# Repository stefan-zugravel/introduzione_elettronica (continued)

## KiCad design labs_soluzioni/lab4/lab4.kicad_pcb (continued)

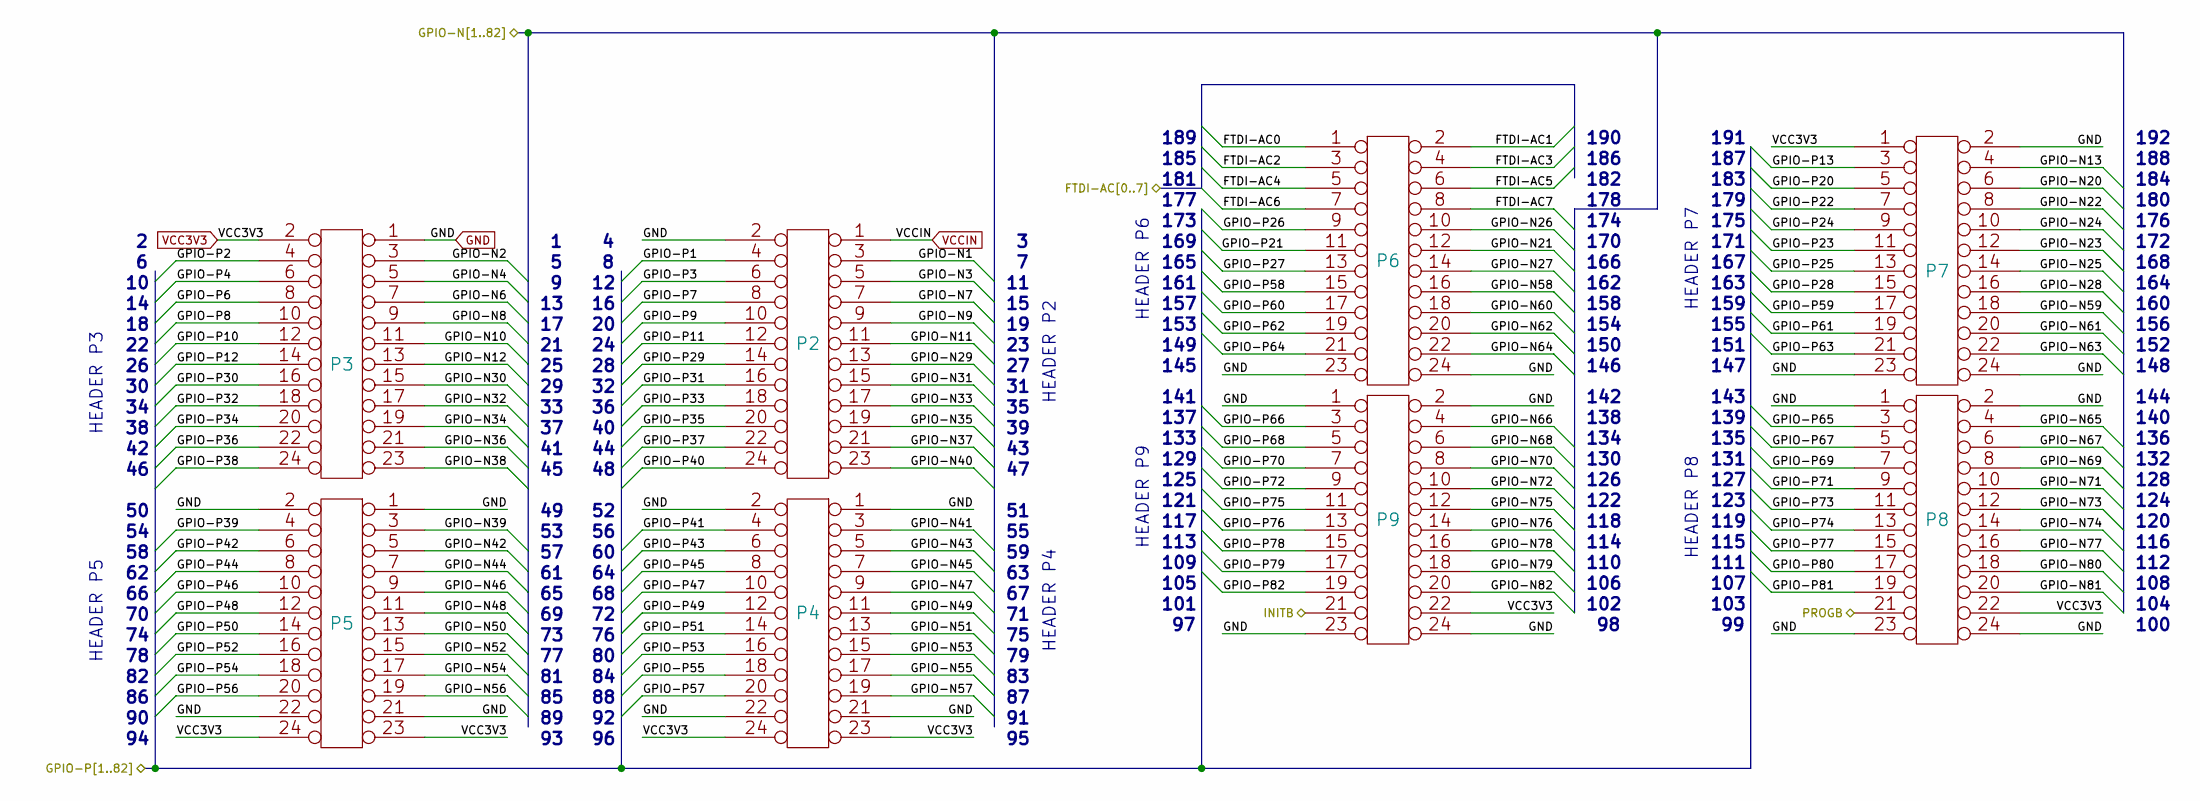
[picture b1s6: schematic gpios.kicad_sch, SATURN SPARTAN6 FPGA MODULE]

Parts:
P2, P3, P4, P5, P6, P7, P8, P9: CONN_12X2

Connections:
/FTDI2232H/FTDI-AC0: P6.1; also elsewhere on the board
/FTDI2232H/FTDI-AC1: P6.2; also elsewhere on the board
/FTDI2232H/FTDI-AC2: P6.3; also elsewhere on the board
/FTDI2232H/FTDI-AC3: P6.4; also elsewhere on the board
/FTDI2232H/FTDI-AC4: P6.5; also elsewhere on the board
/FTDI2232H/FTDI-AC5: P6.6; also elsewhere on the board
/FTDI2232H/FTDI-AC6: P6.7; also elsewhere on the board
/FTDI2232H/FTDI-AC7: P6.8; also elsewhere on the board
/FTDI2232H/PROGB: P8.21; also elsewhere on the board
/GPIOS/GPIO-N1: P2.3; also elsewhere on the board
/GPIOS/GPIO-N2: P3.3; also elsewhere on the board
/GPIOS/GPIO-N3: P2.5; also elsewhere on the board
/GPIOS/GPIO-N4: P3.5; also elsewhere on the board
/GPIOS/GPIO-N6: P3.7; also elsewhere on the board
/GPIOS/GPIO-N7: P2.7; also elsewhere on the board
/GPIOS/GPIO-N8: P3.9; also elsewhere on the board
/GPIOS/GPIO-N9: P2.9; also elsewhere on the board
/GPIOS/GPIO-N10: P3.11; also elsewhere on the board
/GPIOS/GPIO-N11: P2.11; also elsewhere on the board
/GPIOS/GPIO-N12: P3.13; also elsewhere on the board
/GPIOS/GPIO-N13: P7.4; also elsewhere on the board
/GPIOS/GPIO-N20: P7.6; also elsewhere on the board
/GPIOS/GPIO-N21: P6.12; also elsewhere on the board
/GPIOS/GPIO-N22: P7.8; also elsewhere on the board
/GPIOS/GPIO-N23: P7.12; also elsewhere on the board
/GPIOS/GPIO-N24: P7.10; also elsewhere on the board
/GPIOS/GPIO-N25: P7.14; also elsewhere on the board
/GPIOS/GPIO-N26: P6.10; also elsewhere on the board
/GPIOS/GPIO-N27: P6.14; also elsewhere on the board
/GPIOS/GPIO-N28: P7.16; also elsewhere on the board
/GPIOS/GPIO-N29: P2.13; also elsewhere on the board
/GPIOS/GPIO-N30: P3.15; also elsewhere on the board
/GPIOS/GPIO-N31: P2.15; also elsewhere on the board
/GPIOS/GPIO-N32: P3.17; also elsewhere on the board
/GPIOS/GPIO-N33: P2.17; also elsewhere on the board
/GPIOS/GPIO-N34: P3.19; also elsewhere on the board
/GPIOS/GPIO-N35: P2.19; also elsewhere on the board
/GPIOS/GPIO-N36: P3.21; also elsewhere on the board
/GPIOS/GPIO-N37: P2.21; also elsewhere on the board
/GPIOS/GPIO-N38: P3.23; also elsewhere on the board
/GPIOS/GPIO-N39: P5.3; also elsewhere on the board
/GPIOS/GPIO-N40: P2.23; also elsewhere on the board
/GPIOS/GPIO-N41: P4.3; also elsewhere on the board
/GPIOS/GPIO-N42: P5.5; also elsewhere on the board
/GPIOS/GPIO-N43: P4.5; also elsewhere on the board
/GPIOS/GPIO-N44: P5.7; also elsewhere on the board
/GPIOS/GPIO-N45: P4.7; also elsewhere on the board
/GPIOS/GPIO-N46: P5.9; also elsewhere on the board
/GPIOS/GPIO-N47: P4.9; also elsewhere on the board
/GPIOS/GPIO-N48: P5.11; also elsewhere on the board
/GPIOS/GPIO-N49: P4.11; also elsewhere on the board
/GPIOS/GPIO-N50: P5.13; also elsewhere on the board
/GPIOS/GPIO-N51: P4.13; also elsewhere on the board
/GPIOS/GPIO-N52: P5.15; also elsewhere on the board
/GPIOS/GPIO-N53: P4.15; also elsewhere on the board
/GPIOS/GPIO-N54: P5.17; also elsewhere on the board
/GPIOS/GPIO-N55: P4.17; also elsewhere on the board
/GPIOS/GPIO-N56: P5.19; also elsewhere on the board
/GPIOS/GPIO-N57: P4.19; also elsewhere on the board
/GPIOS/GPIO-N58: P6.16; also elsewhere on the board
/GPIOS/GPIO-N59: P7.18; also elsewhere on the board
/GPIOS/GPIO-N60: P6.18; also elsewhere on the board
/GPIOS/GPIO-N61: P7.20; also elsewhere on the board
/GPIOS/GPIO-N62: P6.20; also elsewhere on the board
/GPIOS/GPIO-N63: P7.22; also elsewhere on the board
/GPIOS/GPIO-N64: P6.22; also elsewhere on the board
/GPIOS/GPIO-N65: P8.4; also elsewhere on the board
/GPIOS/GPIO-N66: P9.4; also elsewhere on the board
/GPIOS/GPIO-N67: P8.6; also elsewhere on the board
/GPIOS/GPIO-N68: P9.6; also elsewhere on the board
/GPIOS/GPIO-N69: P8.8; also elsewhere on the board
/GPIOS/GPIO-N70: P9.8; also elsewhere on the board
/GPIOS/GPIO-N71: P8.10; also elsewhere on the board
/GPIOS/GPIO-N72: P9.10; also elsewhere on the board
/GPIOS/GPIO-N73: P8.12; also elsewhere on the board
/GPIOS/GPIO-N74: P8.14; also elsewhere on the board
/GPIOS/GPIO-N75: P9.12; also elsewhere on the board
/GPIOS/GPIO-N76: P9.14; also elsewhere on the board
/GPIOS/GPIO-N77: P8.16; also elsewhere on the board
/GPIOS/GPIO-N78: P9.16; also elsewhere on the board
/GPIOS/GPIO-N79: P9.18; also elsewhere on the board
/GPIOS/GPIO-N80: P8.18; also elsewhere on the board
/GPIOS/GPIO-N81: P8.20; also elsewhere on the board
/GPIOS/GPIO-N82: P9.20; also elsewhere on the board
/GPIOS/GPIO-P1: P2.4; also elsewhere on the board
/GPIOS/GPIO-P2: P3.4; also elsewhere on the board
/GPIOS/GPIO-P3: P2.6; also elsewhere on the board
/GPIOS/GPIO-P4: P3.6; also elsewhere on the board
/GPIOS/GPIO-P6: P3.8; also elsewhere on the board
/GPIOS/GPIO-P7: P2.8; also elsewhere on the board
/GPIOS/GPIO-P8: P3.10; also elsewhere on the board
/GPIOS/GPIO-P9: P2.10; also elsewhere on the board
/GPIOS/GPIO-P10: P3.12; also elsewhere on the board
/GPIOS/GPIO-P11: P2.12; also elsewhere on the board
/GPIOS/GPIO-P12: P3.14; also elsewhere on the board
/GPIOS/GPIO-P13: P7.3; also elsewhere on the board
/GPIOS/GPIO-P20: P7.5; also elsewhere on the board
/GPIOS/GPIO-P21: P6.11; also elsewhere on the board
/GPIOS/GPIO-P22: P7.7; also elsewhere on the board
/GPIOS/GPIO-P23: P7.11; also elsewhere on the board
/GPIOS/GPIO-P24: P7.9; also elsewhere on the board
/GPIOS/GPIO-P25: P7.13; also elsewhere on the board
/GPIOS/GPIO-P26: P6.9; also elsewhere on the board
/GPIOS/GPIO-P27: P6.13; also elsewhere on the board
/GPIOS/GPIO-P28: P7.15; also elsewhere on the board
/GPIOS/GPIO-P29: P2.14; also elsewhere on the board
/GPIOS/GPIO-P30: P3.16; also elsewhere on the board
/GPIOS/GPIO-P31: P2.16; also elsewhere on the board
/GPIOS/GPIO-P32: P3.18; also elsewhere on the board
/GPIOS/GPIO-P33: P2.18; also elsewhere on the board
/GPIOS/GPIO-P34: P3.20; also elsewhere on the board
/GPIOS/GPIO-P35: P2.20; also elsewhere on the board
/GPIOS/GPIO-P36: P3.22; also elsewhere on the board
/GPIOS/GPIO-P37: P2.22; also elsewhere on the board
/GPIOS/GPIO-P38: P3.24; also elsewhere on the board
/GPIOS/GPIO-P39: P5.4; also elsewhere on the board
/GPIOS/GPIO-P40: P2.24; also elsewhere on the board
/GPIOS/GPIO-P41: P4.4; also elsewhere on the board
/GPIOS/GPIO-P42: P5.6; also elsewhere on the board
/GPIOS/GPIO-P43: P4.6; also elsewhere on the board
/GPIOS/GPIO-P44: P5.8; also elsewhere on the board
/GPIOS/GPIO-P45: P4.8; also elsewhere on the board
/GPIOS/GPIO-P46: P5.10; also elsewhere on the board
/GPIOS/GPIO-P47: P4.10; also elsewhere on the board
/GPIOS/GPIO-P48: P5.12; also elsewhere on the board
/GPIOS/GPIO-P49: P4.12; also elsewhere on the board
/GPIOS/GPIO-P50: P5.14; also elsewhere on the board
/GPIOS/GPIO-P51: P4.14; also elsewhere on the board
/GPIOS/GPIO-P52: P5.16; also elsewhere on the board
/GPIOS/GPIO-P53: P4.16; also elsewhere on the board
/GPIOS/GPIO-P54: P5.18; also elsewhere on the board
/GPIOS/GPIO-P55: P4.18; also elsewhere on the board
/GPIOS/GPIO-P56: P5.20; also elsewhere on the board
/GPIOS/GPIO-P57: P4.20; also elsewhere on the board
/GPIOS/GPIO-P58: P6.15; also elsewhere on the board
/GPIOS/GPIO-P59: P7.17; also elsewhere on the board
/GPIOS/GPIO-P60: P6.17; also elsewhere on the board
/GPIOS/GPIO-P61: P7.19; also elsewhere on the board
/GPIOS/GPIO-P62: P6.19; also elsewhere on the board
/GPIOS/GPIO-P63: P7.21; also elsewhere on the board
/GPIOS/GPIO-P64: P6.21; also elsewhere on the board
/GPIOS/GPIO-P65: P8.3; also elsewhere on the board
/GPIOS/GPIO-P66: P9.3; also elsewhere on the board
/GPIOS/GPIO-P67: P8.5; also elsewhere on the board
/GPIOS/GPIO-P68: P9.5; also elsewhere on the board
/GPIOS/GPIO-P69: P8.7; also elsewhere on the board
/GPIOS/GPIO-P70: P9.7; also elsewhere on the board
/GPIOS/GPIO-P71: P8.9; also elsewhere on the board
/GPIOS/GPIO-P72: P9.9; also elsewhere on the board
/GPIOS/GPIO-P73: P8.11; also elsewhere on the board
/GPIOS/GPIO-P74: P8.13; also elsewhere on the board
/GPIOS/GPIO-P75: P9.11; also elsewhere on the board
/GPIOS/GPIO-P76: P9.13; also elsewhere on the board
/GPIOS/GPIO-P77: P8.15; also elsewhere on the board
/GPIOS/GPIO-P78: P9.15; also elsewhere on the board
/GPIOS/GPIO-P79: P9.17; also elsewhere on the board
/GPIOS/GPIO-P80: P8.17; also elsewhere on the board
/GPIOS/GPIO-P81: P8.19; also elsewhere on the board
/GPIOS/GPIO-P82: P9.19; also elsewhere on the board
/GPIOS/INITB: P9.21; also elsewhere on the board
GND: P2.2, P3.1, P4.1, P4.2, P4.21, P4.22, P5.1, P5.2, P5.21, P5.22, P6.23, P6.24, P7.2, P7.23, P7.24, P8.1, P8.2, P8.23, P8.24, P9.1, P9.2, P9.23, P9.24; also elsewhere on the board
VCC3V3: P3.2, P4.23, P4.24, P5.23, P5.24, P7.1, P8.22, P9.22; also elsewhere on the board
VCCIN: P2.1; also elsewhere on the board

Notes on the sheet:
141
129
132
116
112
184
150
187
139
115
100
127
111
179
120
175
183
180
162
154
134
192
157
155
113
101
148
105
HEADER P7
128
176
189
163
107
143
123
174
HEADER P9
190
104

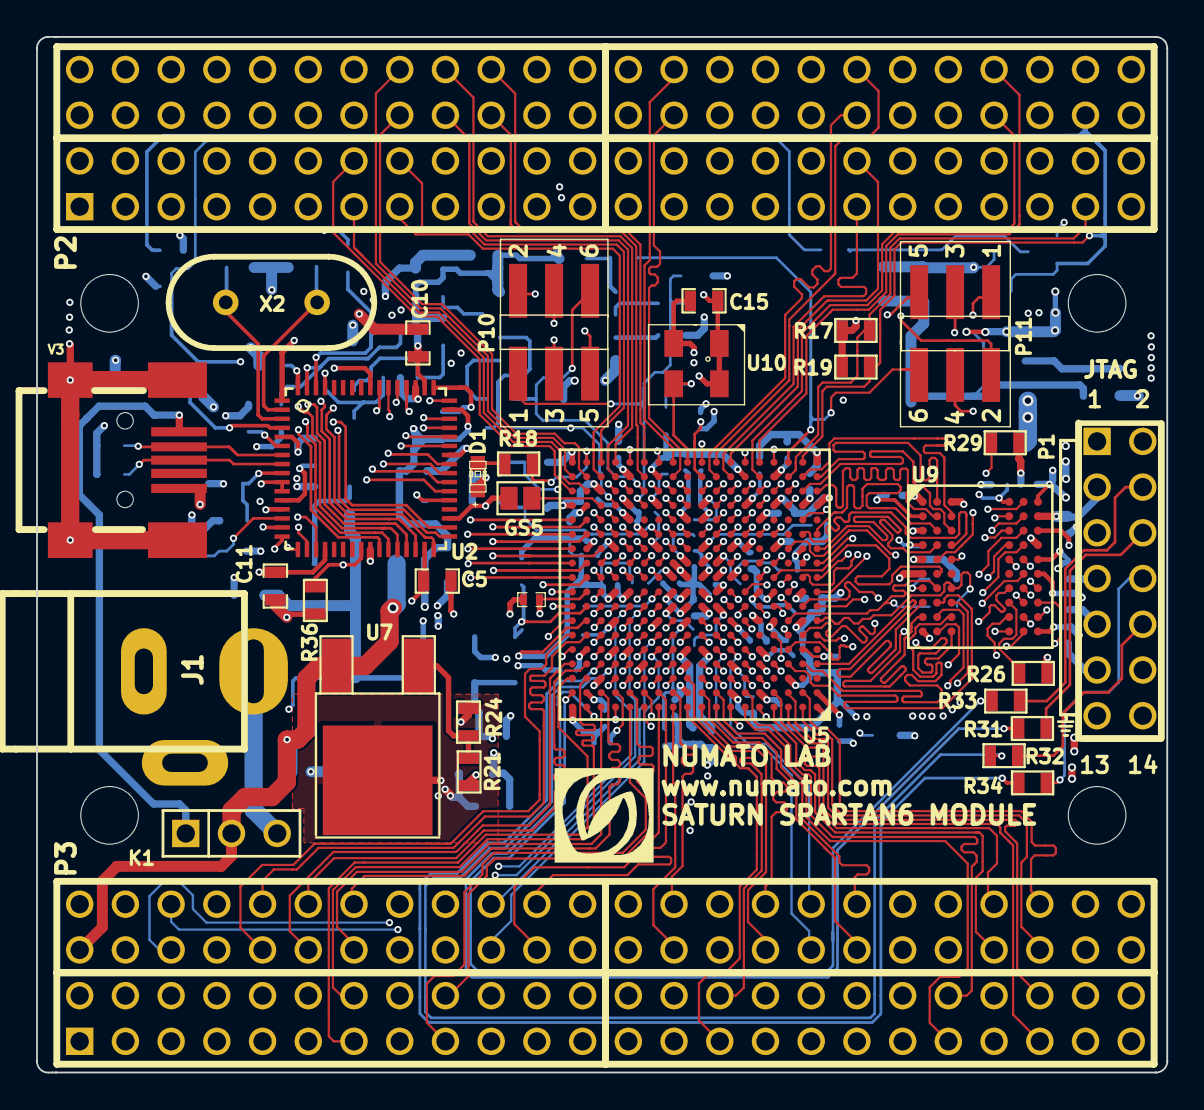
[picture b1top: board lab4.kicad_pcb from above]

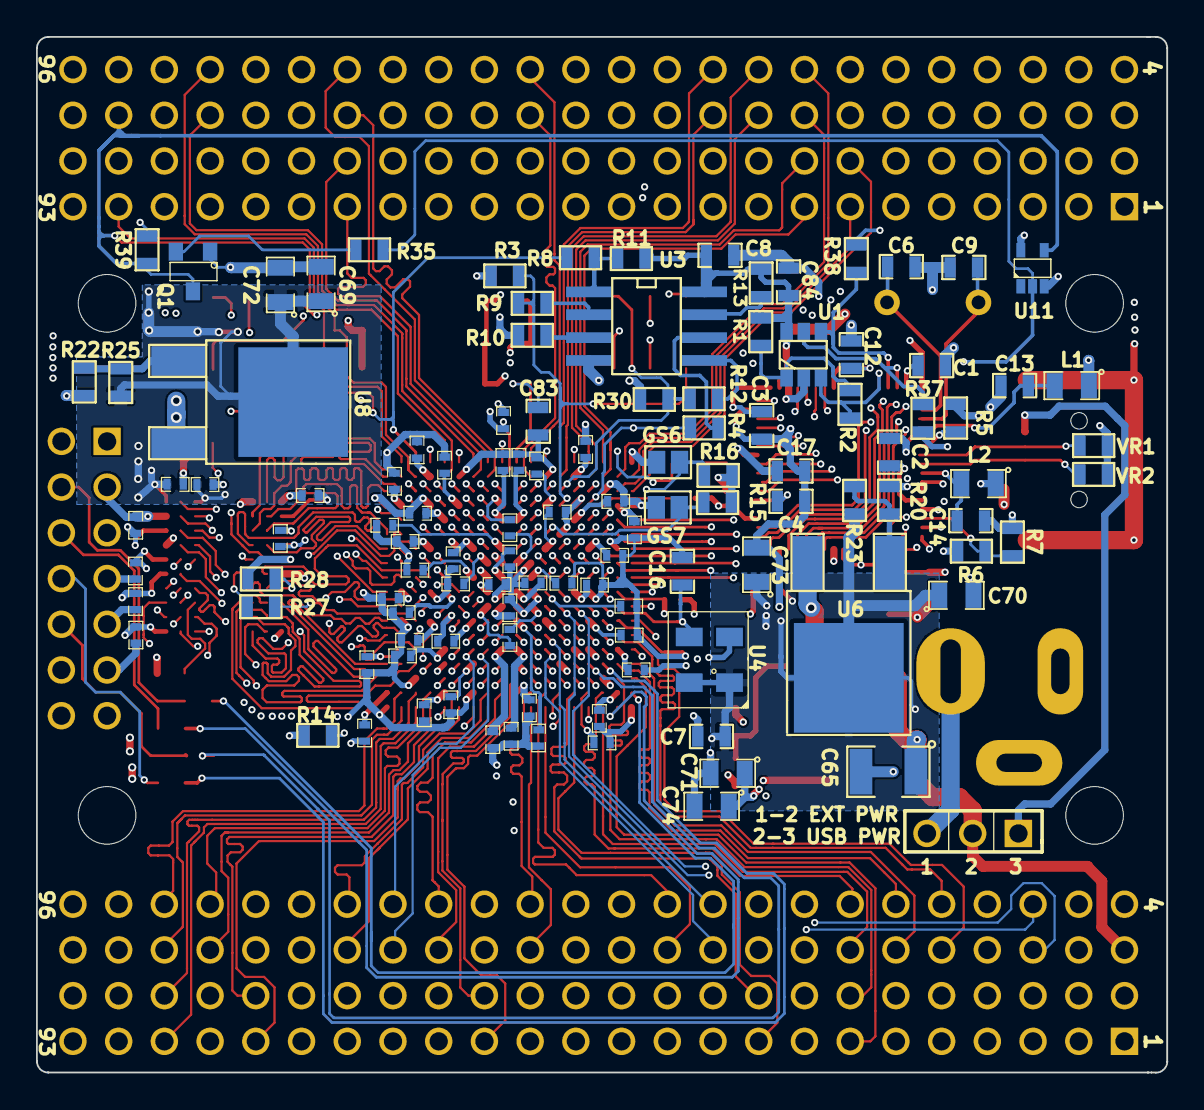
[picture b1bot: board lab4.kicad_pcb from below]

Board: 6 copper layers, 62.8 x 57.5 mm, 157 parts (114 on the bottom side), 271 nets.

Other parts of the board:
1PIN, 1PIN#2, 1PIN#3, 1PIN#4: P***; MH-3.2MM
U5: SPARTAN6LXXXX-CSG324; CSG324

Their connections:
/FTDI2232H/PROGB: U5.V2; also elsewhere on the board
/FTDI2232H/U1-CS: U5.V3; also elsewhere on the board
/FTDI2232H/U1-D0: U5.L17; also elsewhere on the board
/FTDI2232H/U1-D1: U5.L18; also elsewhere on the board
/FTDI2232H/U1-D2: U5.M16; also elsewhere on the board
/FTDI2232H/U1-D3: U5.M18; also elsewhere on the board
/FTDI2232H/U1-D4: U5.N17; also elsewhere on the board
/FTDI2232H/U1-D5: U5.N18; also elsewhere on the board
/FTDI2232H/U1-D6: U5.P17; also elsewhere on the board
/FTDI2232H/U1-D7: U5.P18; also elsewhere on the board
/FTDI2232H/U1-RD#: U5.J18; also elsewhere on the board
/FTDI2232H/U1-RXF#: U5.K18; also elsewhere on the board
/FTDI2232H/U1-SCK: U5.R15; also elsewhere on the board
/FTDI2232H/U1-SDI: U5.R13; also elsewhere on the board
/FTDI2232H/U1-SDO: U5.T13; also elsewhere on the board
/FTDI2232H/U1-SIWUB: U5.H18; also elsewhere on the board
/FTDI2232H/U1-TXE#: U5.K17; also elsewhere on the board
/FTDI2232H/U1-WR#: U5.J16; also elsewhere on the board
/GPIOS/GPIO-N1: U5.K14; also elsewhere on the board
/GPIOS/GPIO-N2: U5.G13; also elsewhere on the board
/GPIOS/GPIO-N3: U5.H14; also elsewhere on the board
/GPIOS/GPIO-N4: U5.H16; also elsewhere on the board
/GPIOS/GPIO-N6: U5.G14; also elsewhere on the board
/GPIOS/GPIO-N7: U5.G18; also elsewhere on the board
/GPIOS/GPIO-N8: U5.F16; also elsewhere on the board
/GPIOS/GPIO-N9: U5.F18; also elsewhere on the board
/GPIOS/GPIO-N10: U5.E18; also elsewhere on the board
/GPIOS/GPIO-N11: U5.D18; also elsewhere on the board
/GPIOS/GPIO-N12: U5.C18; also elsewhere on the board
/GPIOS/GPIO-N13: U5.K13; also elsewhere on the board
/GPIOS/GPIO-N20: U5.M13; also elsewhere on the board
/GPIOS/GPIO-N21: U5.K16; also elsewhere on the board
/GPIOS/GPIO-N22: U5.N14; also elsewhere on the board
/GPIOS/GPIO-N23: U5.N16; also elsewhere on the board
/GPIOS/GPIO-N24: U5.L16; also elsewhere on the board
/GPIOS/GPIO-N25: U5.P16; also elsewhere on the board
/GPIOS/GPIO-N26: U5.L13; also elsewhere on the board
/GPIOS/GPIO-N27: U5.T18; also elsewhere on the board
/GPIOS/GPIO-N28: U5.U18; also elsewhere on the board
/GPIOS/GPIO-N29: U5.A16; also elsewhere on the board
/GPIOS/GPIO-N30: U5.A15; also elsewhere on the board
/GPIOS/GPIO-N31: U5.C14; also elsewhere on the board
/GPIOS/GPIO-N32: U5.A14; also elsewhere on the board
/GPIOS/GPIO-N33: U5.E13; also elsewhere on the board
/GPIOS/GPIO-N34: U5.A13; also elsewhere on the board
/GPIOS/GPIO-N35: U5.E12; also elsewhere on the board
/GPIOS/GPIO-N36: U5.C12; also elsewhere on the board
/GPIOS/GPIO-N37: U5.A12; also elsewhere on the board
/GPIOS/GPIO-N38: U5.E11; also elsewhere on the board
/GPIOS/GPIO-N39: U5.F10; also elsewhere on the board
/GPIOS/GPIO-N40: U5.C11; also elsewhere on the board
/GPIOS/GPIO-N41: U5.A11; also elsewhere on the board
/GPIOS/GPIO-N42: U5.A10; also elsewhere on the board
/GPIOS/GPIO-N43: U5.F9; also elsewhere on the board
/GPIOS/GPIO-N44: U5.C9; also elsewhere on the board
/GPIOS/GPIO-N45: U5.A9; also elsewhere on the board
/GPIOS/GPIO-N46: U5.F8; also elsewhere on the board
/GPIOS/GPIO-N47: U5.E8; also elsewhere on the board
/GPIOS/GPIO-N48: U5.C8; also elsewhere on the board
/GPIOS/GPIO-N49: U5.A8; also elsewhere on the board
/GPIOS/GPIO-N50: U5.E6; also elsewhere on the board
/GPIOS/GPIO-N51: U5.A7; also elsewhere on the board
/GPIOS/GPIO-N52: U5.A6; also elsewhere on the board
/GPIOS/GPIO-N53: U5.C6; also elsewhere on the board
/GPIOS/GPIO-N54: U5.A5; also elsewhere on the board
/GPIOS/GPIO-N55: U5.A4; also elsewhere on the board
/GPIOS/GPIO-N56: U5.A3; also elsewhere on the board
/GPIOS/GPIO-N57: U5.A2; also elsewhere on the board
/GPIOS/GPIO-N58: U5.V16; also elsewhere on the board
/GPIOS/GPIO-N59: U5.V15; also elsewhere on the board
/GPIOS/GPIO-N60: U5.V14; also elsewhere on the board
/GPIOS/GPIO-N61: U5.V13; also elsewhere on the board
/GPIOS/GPIO-N62: U5.V12; also elsewhere on the board
/GPIOS/GPIO-N63: U5.N11; also elsewhere on the board
/GPIOS/GPIO-N64: U5.T11; also elsewhere on the board
/GPIOS/GPIO-N65: U5.V11; also elsewhere on the board
/GPIOS/GPIO-N66: U5.P11; also elsewhere on the board
/GPIOS/GPIO-N67: U5.N9; also elsewhere on the board
/GPIOS/GPIO-N68: U5.T10; also elsewhere on the board
/GPIOS/GPIO-N69: U5.T8; also elsewhere on the board
/GPIOS/GPIO-N70: U5.V9; also elsewhere on the board
/GPIOS/GPIO-N71: U5.N8; also elsewhere on the board
/GPIOS/GPIO-N72: U5.P8; also elsewhere on the board
/GPIOS/GPIO-N73: U5.V8; also elsewhere on the board
/GPIOS/GPIO-N74: U5.P7; also elsewhere on the board
/GPIOS/GPIO-N75: U5.V7; also elsewhere on the board
/GPIOS/GPIO-N76: U5.T7; also elsewhere on the board
/GPIOS/GPIO-N77: U5.V6; also elsewhere on the board
/GPIOS/GPIO-N78: U5.P6; also elsewhere on the board
/GPIOS/GPIO-N79: U5.T5; also elsewhere on the board
/GPIOS/GPIO-N80: U5.V5; also elsewhere on the board
/GPIOS/GPIO-N81: U5.V4; also elsewhere on the board
/GPIOS/GPIO-N82: U5.T3; also elsewhere on the board
/GPIOS/GPIO-P1: U5.J13; also elsewhere on the board
/GPIOS/GPIO-P2: U5.H12; also elsewhere on the board
/GPIOS/GPIO-P3: U5.H13; also elsewhere on the board
/GPIOS/GPIO-P4: U5.H15; also elsewhere on the board
/GPIOS/GPIO-P6: U5.F14; also elsewhere on the board
/GPIOS/GPIO-P7: U5.G16; also elsewhere on the board
/GPIOS/GPIO-P8: U5.F15; also elsewhere on the board
/GPIOS/GPIO-P9: U5.F17; also elsewhere on the board
/GPIOS/GPIO-P10: U5.E16; also elsewhere on the board
/GPIOS/GPIO-P11: U5.D17; also elsewhere on the board
/GPIOS/GPIO-P12: U5.C17; also elsewhere on the board
/GPIOS/GPIO-P13: U5.K12; also elsewhere on the board
/GPIOS/GPIO-P20: U5.L14; also elsewhere on the board
/GPIOS/GPIO-P21: U5.K15; also elsewhere on the board
/GPIOS/GPIO-P22: U5.M14; also elsewhere on the board
/GPIOS/GPIO-P23: U5.N15; also elsewhere on the board
/GPIOS/GPIO-P24: U5.L15; also elsewhere on the board
/GPIOS/GPIO-P25: U5.P15; also elsewhere on the board
/GPIOS/GPIO-P26: U5.L12; also elsewhere on the board
/GPIOS/GPIO-P27: U5.T17; also elsewhere on the board
/GPIOS/GPIO-P28: U5.U17; also elsewhere on the board
/GPIOS/GPIO-P29: U5.B16; also elsewhere on the board
/GPIOS/GPIO-P30: U5.C15; also elsewhere on the board
/GPIOS/GPIO-P31: U5.D14; also elsewhere on the board
/GPIOS/GPIO-P32: U5.B14; also elsewhere on the board
/GPIOS/GPIO-P33: U5.F13; also elsewhere on the board
/GPIOS/GPIO-P34: U5.C13; also elsewhere on the board
/GPIOS/GPIO-P35: U5.F12; also elsewhere on the board
/GPIOS/GPIO-P36: U5.D12; also elsewhere on the board
/GPIOS/GPIO-P37: U5.B12; also elsewhere on the board
/GPIOS/GPIO-P38: U5.F11; also elsewhere on the board
/GPIOS/GPIO-P39: U5.G11; also elsewhere on the board
/GPIOS/GPIO-P40: U5.D11; also elsewhere on the board
/GPIOS/GPIO-P41: U5.B11; also elsewhere on the board
/GPIOS/GPIO-P42: U5.C10; also elsewhere on the board
/GPIOS/GPIO-P43: U5.G9; also elsewhere on the board
/GPIOS/GPIO-P44: U5.D9; also elsewhere on the board
/GPIOS/GPIO-P45: U5.B9; also elsewhere on the board
/GPIOS/GPIO-P46: U5.G8; also elsewhere on the board
/GPIOS/GPIO-P47: U5.E7; also elsewhere on the board
/GPIOS/GPIO-P48: U5.D8; also elsewhere on the board
/GPIOS/GPIO-P49: U5.B8; also elsewhere on the board
/GPIOS/GPIO-P50: U5.F7; also elsewhere on the board
/GPIOS/GPIO-P51: U5.C7; also elsewhere on the board
/GPIOS/GPIO-P52: U5.B6; also elsewhere on the board
/GPIOS/GPIO-P53: U5.D6; also elsewhere on the board
/GPIOS/GPIO-P54: U5.C5; also elsewhere on the board
/GPIOS/GPIO-P55: U5.B4; also elsewhere on the board
/GPIOS/GPIO-P56: U5.B3; also elsewhere on the board
/GPIOS/GPIO-P57: U5.B2; also elsewhere on the board
/GPIOS/GPIO-P58: U5.U16; also elsewhere on the board
/GPIOS/GPIO-P59: U5.U15; also elsewhere on the board
/GPIOS/GPIO-P60: U5.T14; also elsewhere on the board
/GPIOS/GPIO-P61: U5.U13; also elsewhere on the board
/GPIOS/GPIO-P62: U5.T12; also elsewhere on the board
/GPIOS/GPIO-P63: U5.M11; also elsewhere on the board
/GPIOS/GPIO-P64: U5.R11; also elsewhere on the board
/GPIOS/GPIO-P65: U5.U11; also elsewhere on the board
/GPIOS/GPIO-P66: U5.N10; also elsewhere on the board
/GPIOS/GPIO-P67: U5.M10; also elsewhere on the board
/GPIOS/GPIO-P68: U5.R10; also elsewhere on the board
/GPIOS/GPIO-P69: U5.R8; also elsewhere on the board
/GPIOS/GPIO-P70: U5.T9; also elsewhere on the board
/GPIOS/GPIO-P71: U5.M8; also elsewhere on the board
/GPIOS/GPIO-P72: U5.N7; also elsewhere on the board
/GPIOS/GPIO-P73: U5.U8; also elsewhere on the board
/GPIOS/GPIO-P74: U5.N6; also elsewhere on the board
/GPIOS/GPIO-P75: U5.U7; also elsewhere on the board
/GPIOS/GPIO-P76: U5.R7; also elsewhere on the board
/GPIOS/GPIO-P77: U5.T6; also elsewhere on the board
/GPIOS/GPIO-P78: U5.N5; also elsewhere on the board
/GPIOS/GPIO-P79: U5.R5; also elsewhere on the board
/GPIOS/GPIO-P80: U5.U5; also elsewhere on the board
/GPIOS/GPIO-P81: U5.T4; also elsewhere on the board
/GPIOS/GPIO-P82: U5.R3; also elsewhere on the board
/GPIOS/INITB: U5.U3; also elsewhere on the board
/RAM/DDR-A0: U5.J7; also elsewhere on the board
/RAM/DDR-A1: U5.J6; also elsewhere on the board
/RAM/DDR-A2: U5.H5; also elsewhere on the board
/RAM/DDR-A3: U5.L7; also elsewhere on the board
/RAM/DDR-A4: U5.F3; also elsewhere on the board
/RAM/DDR-A5: U5.H4; also elsewhere on the board
/RAM/DDR-A6: U5.H3; also elsewhere on the board
/RAM/DDR-A7: U5.H6; also elsewhere on the board
/RAM/DDR-A8: U5.D2; also elsewhere on the board
/RAM/DDR-A9: U5.D1; also elsewhere on the board
/RAM/DDR-A10: U5.F4; also elsewhere on the board
/RAM/DDR-A11: U5.D3; also elsewhere on the board
/RAM/DDR-A12: U5.G6; also elsewhere on the board
/RAM/DDR-BA0: U5.F2; also elsewhere on the board
/RAM/DDR-BA1: U5.F1; also elsewhere on the board
/RAM/DDR-CAS: U5.K5; also elsewhere on the board
/RAM/DDR-CKE: U5.H7; also elsewhere on the board
/RAM/DDR-CK_N: U5.G1; also elsewhere on the board
/RAM/DDR-CK_P: U5.G3; also elsewhere on the board
/RAM/DDR-D0: U5.L2; also elsewhere on the board
/RAM/DDR-D1: U5.L1; also elsewhere on the board
/RAM/DDR-D2: U5.K2; also elsewhere on the board
/RAM/DDR-D3: U5.K1; also elsewhere on the board
/RAM/DDR-D4: U5.H2; also elsewhere on the board
/RAM/DDR-D5: U5.H1; also elsewhere on the board
/RAM/DDR-D6: U5.J3; also elsewhere on the board
/RAM/DDR-D7: U5.J1; also elsewhere on the board
/RAM/DDR-D8: U5.M3; also elsewhere on the board
/RAM/DDR-D9: U5.M1; also elsewhere on the board
/RAM/DDR-D10: U5.N2; also elsewhere on the board
/RAM/DDR-D11: U5.N1; also elsewhere on the board
/RAM/DDR-D12: U5.T2; also elsewhere on the board
/RAM/DDR-D13: U5.T1; also elsewhere on the board
/RAM/DDR-D14: U5.U2; also elsewhere on the board
/RAM/DDR-D15: U5.U1; also elsewhere on the board
/RAM/DDR-LDM: U5.K3; also elsewhere on the board
/RAM/DDR-LDQS: U5.L4; also elsewhere on the board
/RAM/DDR-RAS: U5.L5; also elsewhere on the board
/RAM/DDR-UDM: U5.K4; also elsewhere on the board
/RAM/DDR-UDQS: U5.P2; also elsewhere on the board
/RAM/DDR-WE: U5.E3; also elsewhere on the board
/RAM/RZQ: U5.N4; also elsewhere on the board
/SPARTAN6/DONE: U5.V17; also elsewhere on the board
/SPARTAN6/GCLK1: U5.V10; also elsewhere on the board
/SPARTAN6/GCLK2: U5.H17; also elsewhere on the board
/SPARTAN6/HSWAP: U5.D4; also elsewhere on the board
/SPARTAN6/M0: U5.T15; also elsewhere on the board
/SPARTAN6/M1: U5.N12; also elsewhere on the board
/SPARTAN6/SUSPEND: U5.R16; also elsewhere on the board
DDR1V8: U5.E2, U5.G4, U5.J2, U5.J5, U5.M4, U5.R2; also elsewhere on the board
GND: U5.A1, U5.A18, U5.B7, U5.B13, U5.C3, U5.C16, U5.D5, U5.D10, U5.E15, U5.G2, U5.G5, U5.G12, U5.G17, U5.H8, U5.H10, U5.J4, U5.J9, U5.J11, U5.J15, U5.K8, U5.K10, U5.L9, U5.L11, U5.M2, U5.M6, U5.M17, U5.N13, U5.R1, U5.R4, U5.R9, U5.R14, U5.R18, U5.T16, U5.U6, U5.U12, U5.V1, U5.V18; also elsewhere on the board
unnamed 257: U5.A17; also elsewhere on the board
unnamed 258: U5.D16; also elsewhere on the board
unnamed 259: U5.D15; also elsewhere on the board
unnamed 260: U5.B18; also elsewhere on the board
VCC1V2: U5.G7, U5.H9, U5.H11, U5.J8, U5.J10, U5.K9, U5.K11, U5.L8, U5.L10, U5.M7, U5.M12; also elsewhere on the board
VCC3V3: U5.B1, U5.B5, U5.B10, U5.B15, U5.B17, U5.D7, U5.D13, U5.E5, U5.E9, U5.E10, U5.E14, U5.E17, U5.G10, U5.G15, U5.J12, U5.J14, U5.J17, U5.K7, U5.M9, U5.M15, U5.P5, U5.P9, U5.P10, U5.P14, U5.R6, U5.R12, U5.R17, U5.U4, U5.U9, U5.U14; also elsewhere on the board

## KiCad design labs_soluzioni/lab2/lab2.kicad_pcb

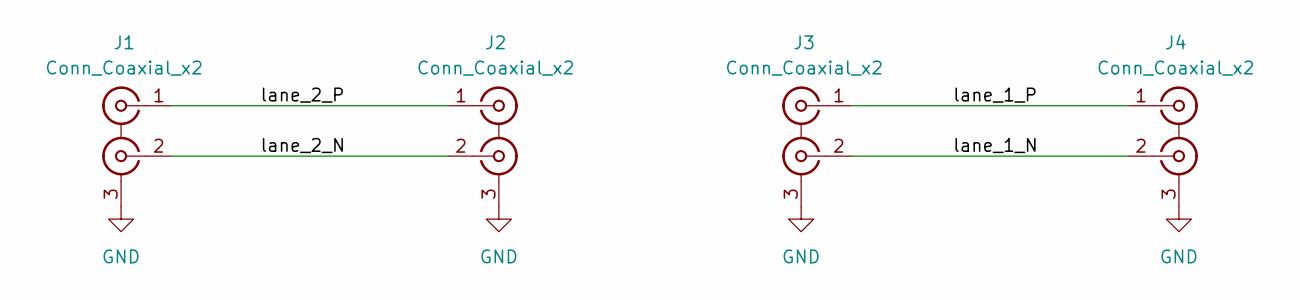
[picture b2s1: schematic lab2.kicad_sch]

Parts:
J1, J2, J3, J4: Conn_Coaxial_x2; LEMO-EPG.00.302.NLN

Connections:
/lane_1_N: J3.2 (IN2), J4.2 (IN2)
/lane_1_P: J3.1 (IN1), J4.1 (IN1)
/lane_2_N: J1.2 (IN2), J2.2 (IN2)
/lane_2_P: J1.1 (IN1), J2.1 (IN1)
GND: J1.3 (EXT), J2.3 (EXT), J3.3 (EXT), J4.3 (EXT)

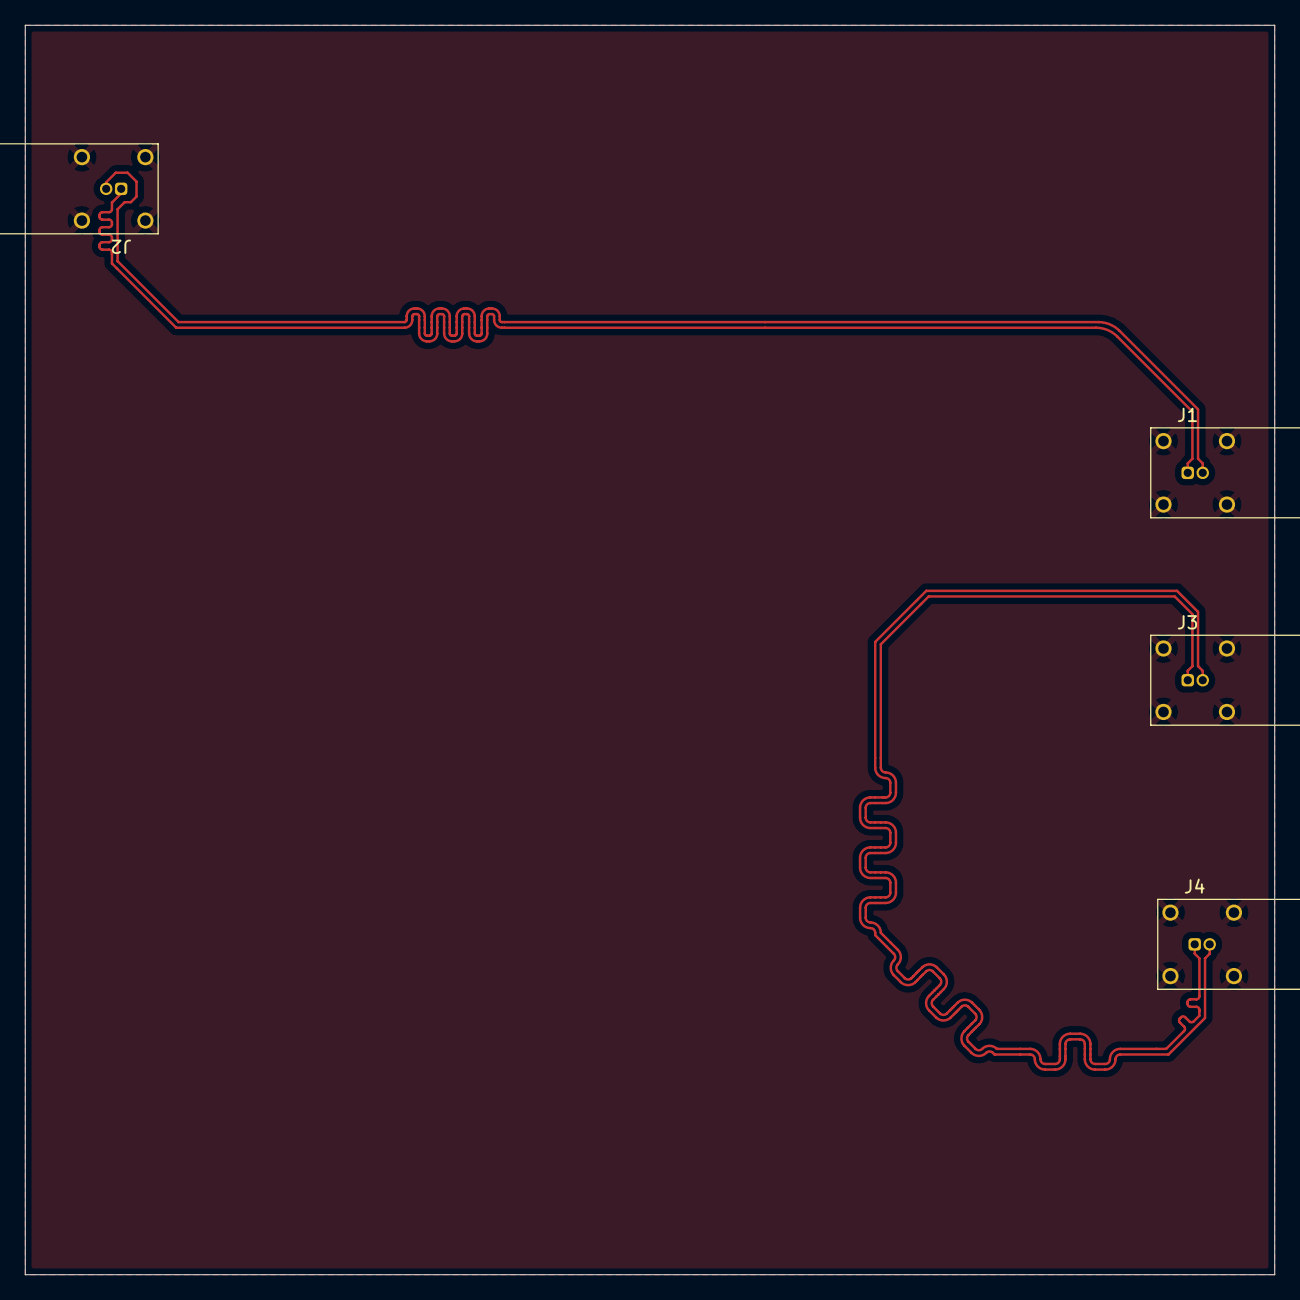
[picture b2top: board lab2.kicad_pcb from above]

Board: 2 copper layers, 100.0 x 100.0 mm, 4 parts (0 on the bottom side), 5 nets.

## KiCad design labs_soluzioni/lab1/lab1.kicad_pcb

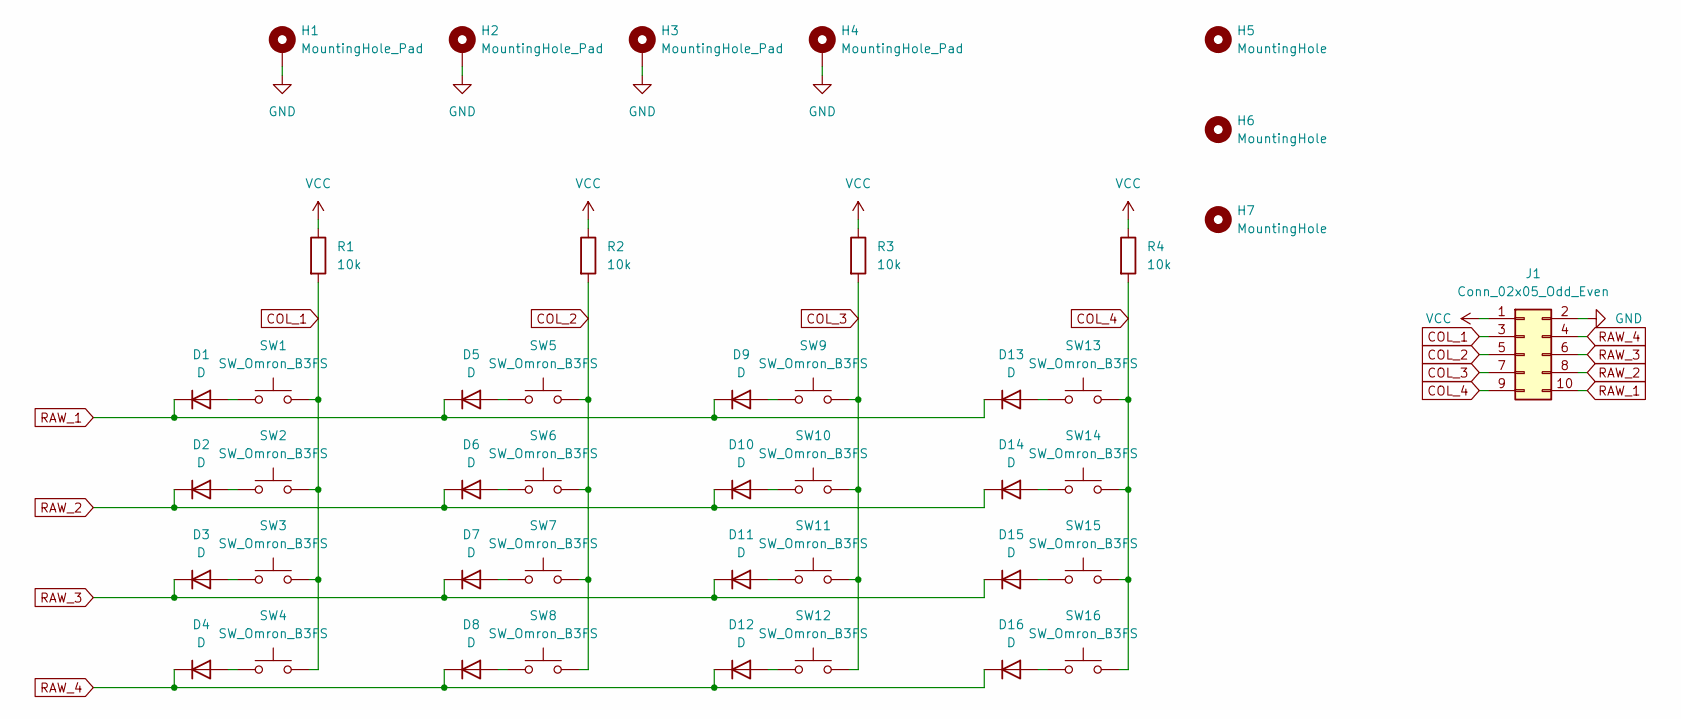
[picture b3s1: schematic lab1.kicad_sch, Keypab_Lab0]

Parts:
D1, D2, D3, D4, D5, D6, D7, D8, D9, D10, D11, D12, D13, D14, D15, D16: D; D_0603_1608Metric
H1, H2, H3, H4: MountingHole_Pad; MountingHole_3.2mm_M3_Pad_Via
H5, H6, H7: MountingHole; ToolingHole_1.152mm
J1: Conn_02x05_Odd_Even; PinHeader_2x05_P2.54mm_Vertical
R1, R2, R3, R4: 10k; R_0603_1608Metric
SW1, SW2, SW3, SW4, SW5, SW6, SW7, SW8, SW9, SW10, SW11, SW12, SW13, SW14, SW15, SW16: SW_Omron_B3FS; SW_PUSH_6mm

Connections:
COL_1: J1.3, R1.2, SW1.2, SW2.2, SW3.2, SW4.2
COL_2: J1.5, R2.2, SW5.2, SW6.2, SW7.2, SW8.2
COL_3: J1.7, R3.2, SW9.2, SW10.2, SW11.2, SW12.2
COL_4: J1.9, R4.2, SW13.2, SW14.2, SW15.2, SW16.2
GND: H1.1, H2.1, H3.1, H4.1, J1.2
unnamed: D1.2 (A), SW1.1
unnamed: D2.2 (A), SW2.1
unnamed: D3.2 (A), SW3.1
unnamed: D4.2 (A), SW4.1
unnamed: D5.2 (A), SW5.1
unnamed: D6.2 (A), SW6.1
unnamed: D7.2 (A), SW7.1
unnamed: D8.2 (A), SW8.1
unnamed: D9.2 (A), SW9.1
unnamed: D10.2 (A), SW10.1
unnamed: D11.2 (A), SW11.1
unnamed: D12.2 (A), SW12.1
unnamed: D13.2 (A), SW13.1
unnamed: D14.2 (A), SW14.1
unnamed: D15.2 (A), SW15.1
unnamed: D16.2 (A), SW16.1
RAW_1: D1.1 (K), D5.1 (K), D9.1 (K), D13.1 (K), J1.10
RAW_2: D2.1 (K), D6.1 (K), D10.1 (K), D14.1 (K), J1.8
RAW_3: D3.1 (K), D7.1 (K), D11.1 (K), D15.1 (K), J1.6
RAW_4: D4.1 (K), D8.1 (K), D12.1 (K), D16.1 (K), J1.4
VCC: J1.1, R1.1, R2.1, R3.1, R4.1
